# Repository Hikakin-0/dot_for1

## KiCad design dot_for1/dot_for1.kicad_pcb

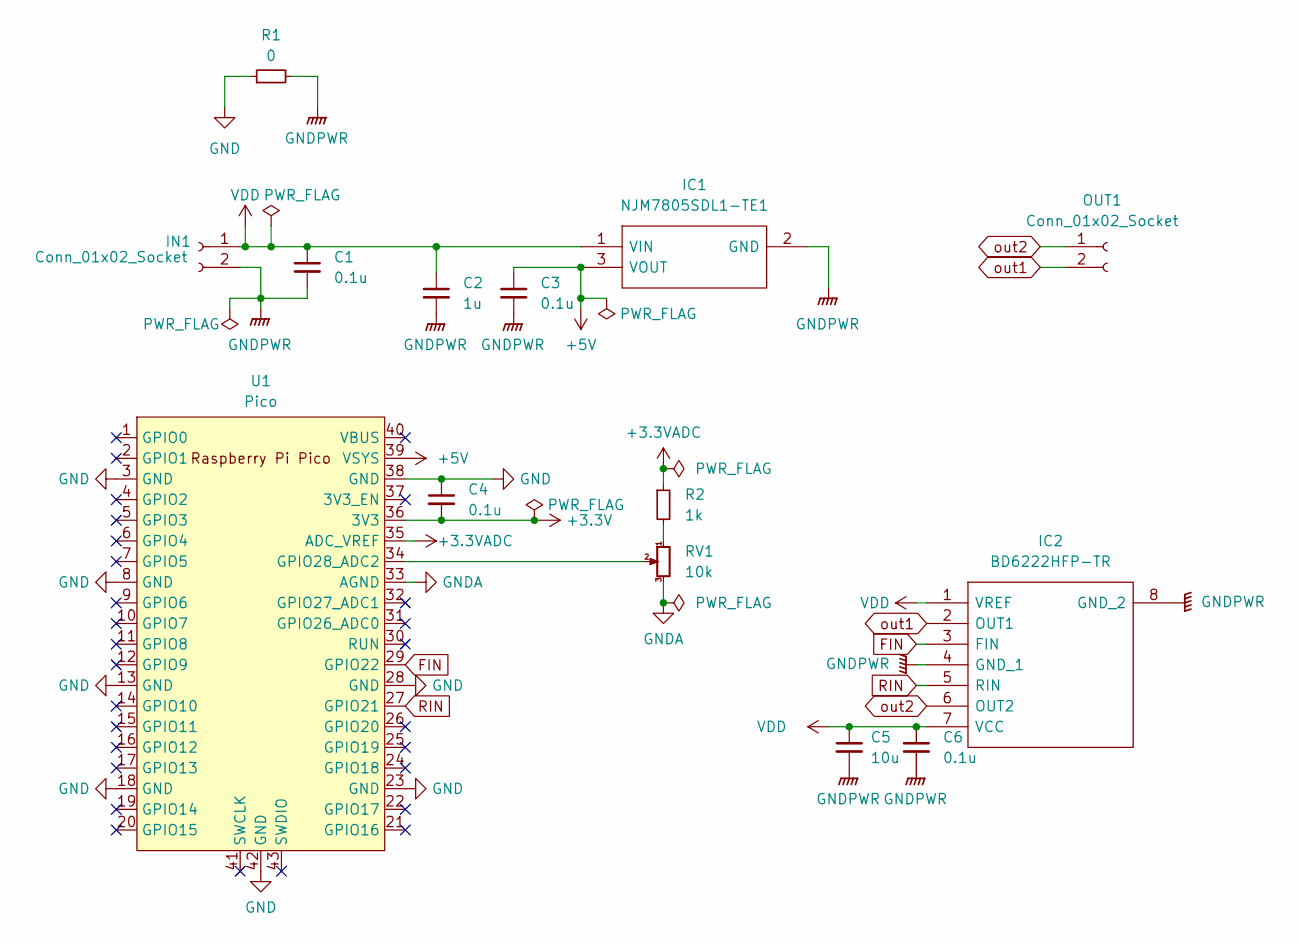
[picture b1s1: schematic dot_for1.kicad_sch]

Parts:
C1, C3, C4, C6: 0.1u; C_0603_1608Metric
C2: 1u; C_0603_1608Metric
C5: 10u; C_0603_1608Metric
IC1: NJM7805SDL1-TE1; NJM7805SDL1TE1; Manufacturer_Part_Number NJM7805SDL1-TE1; Mouser Part Number 513-NJM7805SDL1-TE1
IC2: BD6222HFP-TR; BD6222HFPTR; Manufacturer_Part_Number BD6222HFP-TR
IN1: Conn_01x02_Socket; JST_VH_B2P-VH-FB-B_1x02_P3.96mm_Vertical
OUT1: Conn_01x02_Socket; JST_VH_B2P-VH-FB-B_1x02_P3.96mm_Vertical
R1: 0; R_0402_1005Metric
R2: 1k; R_0402_1005Metric
RV1: 10k; JST_VH_B3P-VH-FB-B_1x03_P3.96mm_Vertical
U1: Pico; RPi_Pico_SMD_TH

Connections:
+3.3V: C4.2, U1.36 (3V3)
+3.3VADC: R2.1, U1.35 (ADC_VREF)
+5V: C3.1, IC1.3 (VOUT), U1.39 (VSYS)
FIN: IC2.3 (FIN), U1.29 (GPIO22)
GND: C4.1, R1.1, U1.3 (GND), U1.8 (GND), U1.13 (GND), U1.18 (GND), U1.23 (GND), U1.28 (GND), U1.38 (GND), U1.42 (GND)
GNDA: RV1.3, U1.33 (AGND)
GNDPWR: C1.2, C2.2, C3.2, C5.2, C6.2, IC1.2 (GND), IC2.4 (GND_1), IC2.8 (GND_2), IN1.2, R1.2
unnamed: R2.2, RV1.1
unnamed: RV1.2, U1.34 (GPIO28_ADC2)
RIN: IC2.5 (RIN), U1.27 (GPIO21)
VDD: C1.1, C2.1, C5.1, C6.1, IC1.1 (VIN), IC2.1 (VREF), IC2.7 (VCC), IN1.1
out1: IC2.2 (OUT1), OUT1.2
out2: IC2.6 (OUT2), OUT1.1

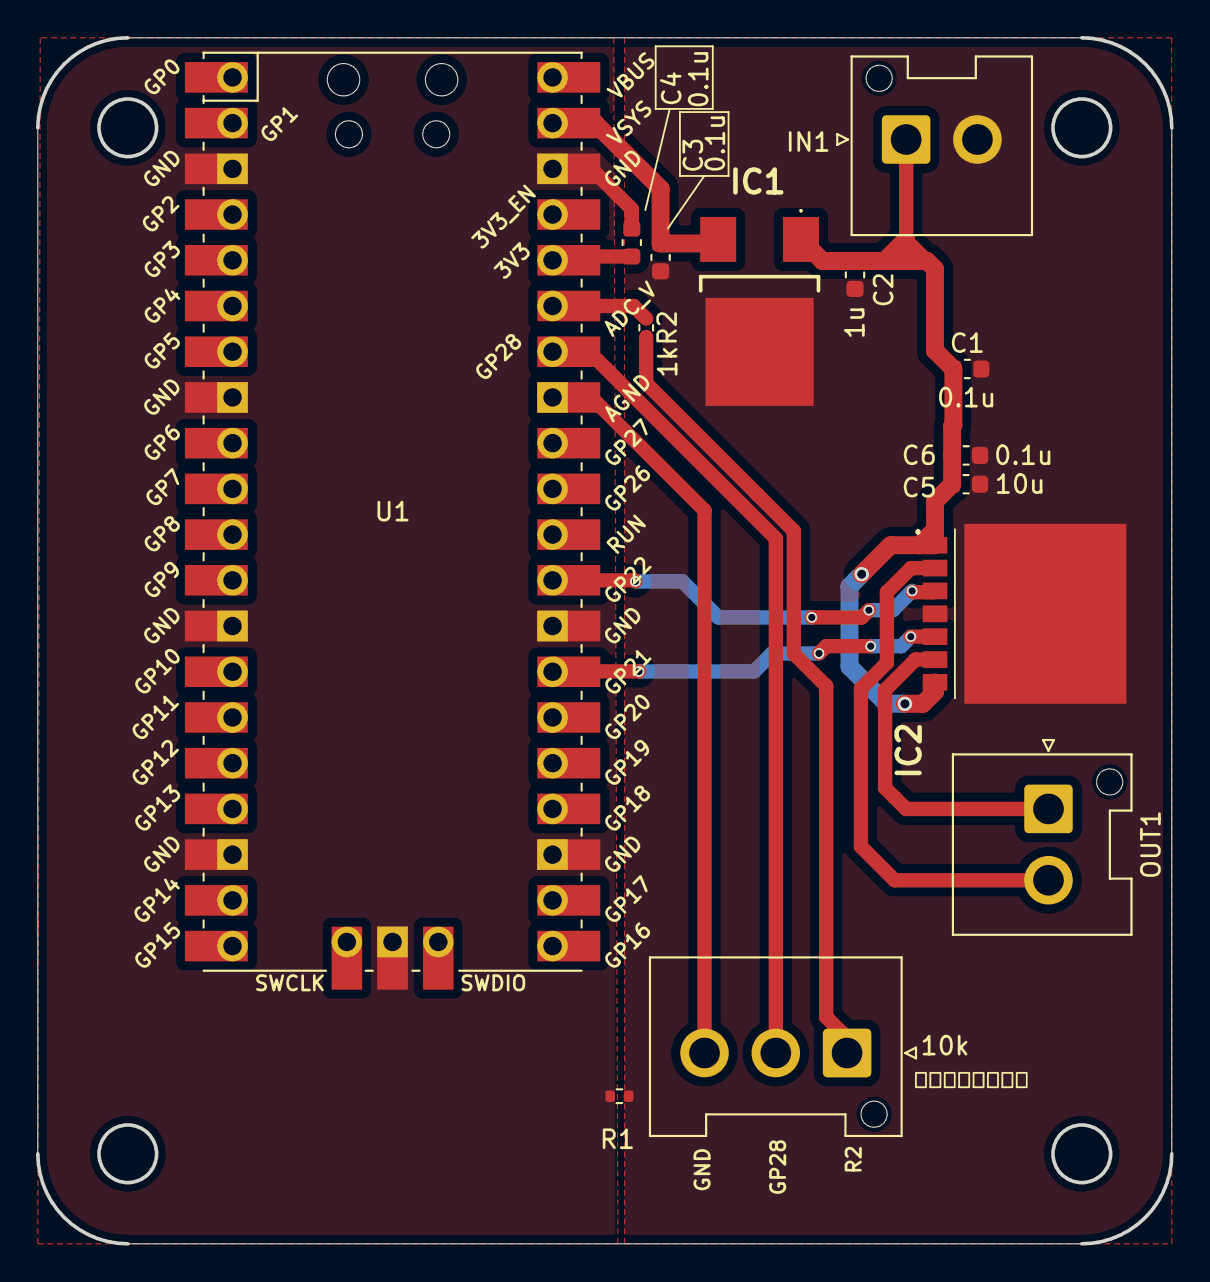
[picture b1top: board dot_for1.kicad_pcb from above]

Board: 2 copper layers, 63.0 x 67.0 mm, 14 parts (0 on the bottom side), 13 nets.
